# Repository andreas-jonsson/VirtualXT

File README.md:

# VirtualXT

VirtualXT is a Turbo PC/XT emulator for [libretro](https://www.libretro.com) that runs on modern hardware, operating systems and bare-metal ARM SBCs.
It is designed to be simple and lightweight yet still capable enough to run a large library of old application and games.

Browser version is avalible [here](https://realmode.games).

## Features

* Intel 286 processor
* PC/XT chipset
* Hardware CPU validator
* CGA or VGA compatible graphics
* EMS and UMA memory
* AdLib music synthesizer
* Serial UARTs
* Ethernet adapter
* Runs on bare-metal ARM
* Direct file share with host
* ISA passthrough​ using Arstech USB2ISA adapter
* GLaBIOS or Turbo XT BIOS 3.1 with extensions
* Integerated GDB server
* Flexible module system
* and more...

## Screenshots

## Build

The emulator is written in [Odin](https://odin-lang.org) and can be compiled using the included GNU Makefile.

```
git clone https://github.com/virtualxt/virtualxt.git
cd virtualxt
make release
# Or if you have RetroArch installed.
make run
```

You can download pre-built binaries from [itch.io](https://phix.itch.io/virtualxt/purchase).

## ISA Passthrough​

VirtualXT supports ISA passthrough using Arstech [USB2ISA](https://arstech.com/install/ecom-catshow/usb2.0.html) adapter or the [CH367](https://www.aliexpress.com/item/1005003569540792.html) development board.
It should be noted that DMA currently not supported and the CH367 board is **VERY** limited in it's capabilities.

## Hardware Validation

A hardware validator was developed to ensure proper CPU behaviour.
Some additional information about that can be found [here](https://hackaday.io/project/184209-virtualxt-hardware-validator).
This [talk](https://youtu.be/qatzd0niz9A?si=_NVqQu_zc1KDB8W6) by Daniel Balsom describes the process in details.

## Shout-out

Friends, contributors and sources of inspiration!

* **gloriouscow**
* **homebrew8088**
* **fmahnke**
* **adriancable**
* **mikechambers84**
* **trylle**
* **640-KB**

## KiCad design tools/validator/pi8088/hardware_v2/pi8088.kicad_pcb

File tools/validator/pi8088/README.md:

# PI8088 Hardware Validator

This is a hardware validator for testing instruction accuracy in 8088/V20 PC emulators. It plugs in the top/back of an RaspberryPi 4/400 computer and was built for testing the VirtualXT IBM PC/XT emulator. But it can easily be adopted for use with other emulators as well.

## Hardware
The hardware is very simple for this project. It is just a passive PCB that attaches to the RaspberryPi and connects any CMOS 8088 compatible CPU, like the 80C88 or NEC V20 to the RaspberryPi's GPIO pins. Something that should be noted is that the system is running on 3.3V and not 5V. Although that is out of spec for the CPU's in question it seems to run completely stable in the frequencies used here. 

## Software
On a software level the system works by first executing a setup programs that loads a CPU state that match the emulators state before the instruction in question was executed. It then lets the instruction execute on the attached CPU. Then proceeds by running a serialization program that retrieves the correct CPU state and compares it with the emulator's state after instruction execution. The user will then be presented with the diffs if any are found.

## Limitations
Although the cycle counts are reported, there are (at least in theory) situations where the exact count can not be trusted. The CPU is running in minimum mode which makes it hard to determine the exact status. For example, if a prefetch is performed during execution it is very complicated to determine how long the actual execution of the instruction took. It might be possible to resolve if the CPU is executing in maximum mode but that requires hardware changes. Software adjustments is needed if you want to test a V20 since not all status signals are decoded and the bus behavior is a little different.

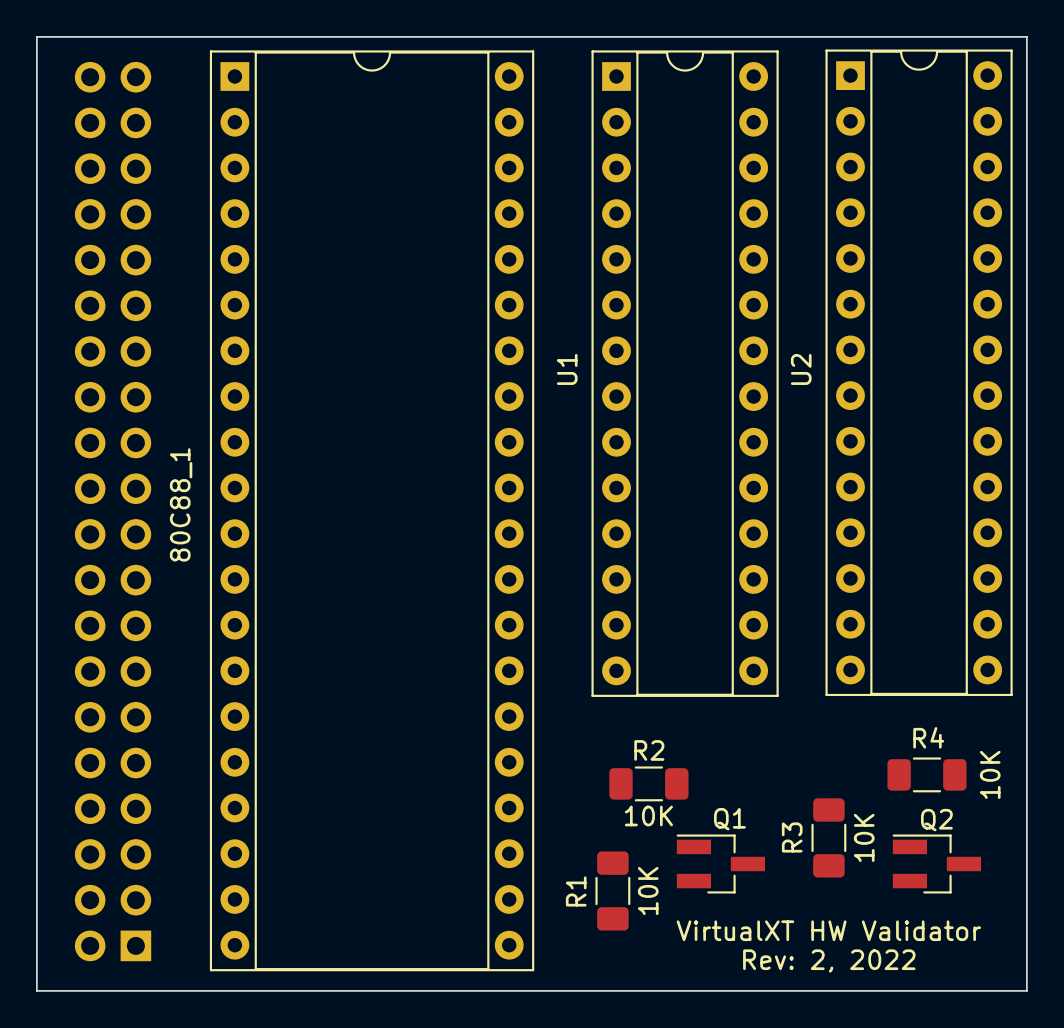
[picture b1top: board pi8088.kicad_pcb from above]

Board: 2 copper layers, 55.0 x 53.0 mm, 10 parts (1 on the bottom side), 35 nets, no tracks yet.

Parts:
80C88_1: 8088_Min_Mode; DIP-40_W15.24mm_Socket
GPIO_1: Raspberry_Pi_2_3; PinSocket_2x20_P2.54mm_Vertical
Q1, Q2: BSS138; SOT-23_Handsoldering
R1, R2, R3, R4: 10K; R_1206_3216Metric_Pad1.30x1.75mm_HandSolder
U1, U2: MCP23017_SP; DIP-28_W7.62mm_Socket

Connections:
/lv_shift/HV: 80C88_1.22 (READY), 80C88_1.33 (MN/~MX), 80C88_1.40 (VCC), GPIO_1.2 (5V), GPIO_1.4 (5V), R2.1, R4.1, U1.9 (VDD), U1.15 (A0), U2.9 (VDD)
/lv_shift/HVD1: Q1.3 (D), R2.2, U1.13 (SDA), U2.13 (SDA)
/lv_shift/HVD2: Q2.3 (D), R4.2, U1.12 (SCK), U2.12 (SCK)
/lv_shift/LV: GPIO_1.1 (3V3), GPIO_1.17 (3V3), Q1.1 (G), Q2.1 (G), R1.1, R3.1
/lv_shift/LVD1: GPIO_1.27 (ID_SD/GPIO0), Q1.2 (S), R1.2
/lv_shift/LVD2: GPIO_1.28 (ID_SC/GPIO1), Q2.2 (S), R3.2
unnamed: 80C88_1.1 (GND), 80C88_1.17 (NMI), 80C88_1.18 (INTR), 80C88_1.20 (GND), 80C88_1.31 (HOLD), GPIO_1.6 (GND), GPIO_1.9 (GND), GPIO_1.14 (GND), GPIO_1.20 (GND), GPIO_1.25 (GND), GPIO_1.30 (GND), GPIO_1.34 (GND), GPIO_1.39 (GND), U1.10 (VSS), U1.16 (A1), U1.17 (A2), U2.10 (VSS), U2.15 (A0), U2.16 (A1), U2.17 (A2)
unnamed: 80C88_1.2 (A14), U2.27 (GPA6)
unnamed: 80C88_1.3 (A13), U2.26 (GPA5)
unnamed: 80C88_1.4 (A12), U2.25 (GPA4)
unnamed: 80C88_1.5 (A11), U2.24 (GPA3)
unnamed: 80C88_1.6 (A10), U2.23 (GPA2)
unnamed: 80C88_1.7 (A9), U2.22 (GPA1)
unnamed: 80C88_1.8 (A8), U2.21 (GPA0)
unnamed: 80C88_1.9 (AD7), U2.8 (GPB7)
unnamed: 80C88_1.10 (AD6), U2.7 (GPB6)
unnamed: 80C88_1.11 (AD5), U2.6 (GPB5)
unnamed: 80C88_1.12 (AD4), U2.5 (GPB4)
unnamed: 80C88_1.13 (AD3), U2.4 (GPB3)
unnamed: 80C88_1.14 (AD2), U2.3 (GPB2)
unnamed: 80C88_1.15 (AD1), U2.2 (GPB1)
unnamed: 80C88_1.16 (AD0), U2.1 (GPB0)
unnamed: 80C88_1.19 (CLK), U1.5 (GPB4)
unnamed: 80C88_1.21 (RESET), U1.6 (GPB5)
unnamed: 80C88_1.23 (~TEST), U1.8 (GPB7)
unnamed: 80C88_1.25 (ALE), U1.7 (GPB6)
unnamed: 80C88_1.28 (IO/~M), U1.22 (GPA1)
unnamed: 80C88_1.29 (WR), U1.23 (GPA2)
unnamed: 80C88_1.32 (~RD), U1.24 (GPA3)
unnamed: 80C88_1.34 (~SSO), U1.21 (GPA0)
unnamed: 80C88_1.35 (A19/S6), U1.4 (GPB3)
unnamed: 80C88_1.36 (A18/S5), U1.3 (GPB2)
unnamed: 80C88_1.37 (A17/S4), U1.2 (GPB1)
unnamed: 80C88_1.38 (A16/S3), U1.1 (GPB0)
unnamed: 80C88_1.39 (A15), U2.28 (GPA7)

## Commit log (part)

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2023-09-06 First pass on Covox audio. WIP
2023-09-06 Deploying to gh-pages from @ andreas-jonsson/virtualxt@b364c19d4e3e002a4dcddade87100b181e20312b 🚀
2023-09-07 Reworked search paths.
2023-09-07 Changed buffer size.
2023-09-07 Resized buffer
2023-09-12 Added new CPU tests.
2023-09-12 Test cancelation
2023-09-12 Optimized premake script
2023-09-13 Switched to binary tests
2023-09-13 Use cppcheck --force
2023-09-14 Fixed bug in opcode FF.6
2023-09-15 Fixed a few more issues based on new tests.
2023-09-15 Added cycle check
2023-09-15 Exclude devices from test.
2023-09-15 Updated test excludes
2023-09-18 Added some minimal libc things.
2023-09-18 Deploying to gh-pages from @ andreas-jonsson/virtualxt@81c9cbf48ade9e95358b3b4b30e3ac53c2aac271 🚀
2023-09-18 Deploying to gh-pages from @ andreas-jonsson/virtualxt@b7076395af9b6c8488e11fbec7cf9625680b02ff 🚀
2023-09-18 Deploying to gh-pages from @ andreas-jonsson/virtualxt@1f78fcf46ec33975ce1083867473015214faf920 🚀
2023-09-18 SCANF_DISABLE_SUPPORT_FLOAT for now.
2023-09-22 Added frequency function to lua module
2023-09-22 Fixed name collision
2023-09-27 Should return 0 when started with --locate
2023-09-28 Updated version number
2023-10-07 Enable compilation for more unix platforms
2023-10-10 Updated version number.
2023-10-11 A better fix for relative lib loading
2023-10-11 rpath fix for OSX
2023-10-18 Bump @babel/traverse from 7.20.12 to 7.23.2 in /lib/simple-keyboard
    Bumps [@babel/traverse](https://github.com/babel/babel/tree/HEAD/packages/babel-traverse) from 7.20.12 to 7.23.2.
    - [Release notes](https://github.com/babel/babel/releases)
    - [Changelog](https://github.com/babel/babel/blob/main/CHANGELOG.md)
    - [Commits](https://github.com/babel/babel/commits/v7.23.2/packages/babel-traverse)
    ---
    updated-dependencies:
2023-10-19 Removed FDC module and updated ELKS image
2023-10-22 Improved EGA support
2023-10-23 VGA DAC fixes
2023-10-25 Deploying to gh-pages from @ andreas-jonsson/virtualxt@1660b8ebf0dce990bcef757dcaff9782873fdadf 🚀
2023-10-25 Removed CGA mode ctrl register from VGA module
2023-10-26 Fixed broken mode 13
2023-10-27 Default to VGA
2023-10-27 Fixed CGA init on web frontend
2023-10-28 Added turbo switch
2023-10-28 Default to V20
2023-10-29 Changed default frequency.
2023-11-01 update libretro makefile for newer emscripten sdk
2023-11-02 Fixed build issue on web frontend
2023-11-02 Fixed libretro compile issue
2023-11-02 Deploying to gh-pages from @ andreas-jonsson/virtualxt@5f3412cd23ef2f29018911460c91349cd1241ffc 🚀
2023-11-04 Added support for multiple fonts
2023-11-06 Added turbo text
2023-11-06 Fixed frequency switch code
2023-11-06 Added version number to help screen
2023-11-06 Updated SDL version
2023-11-08 Default to CGA
2023-11-08 Deploying to gh-pages from @ andreas-jonsson/virtualxt@6611c641465fa088d2752cda78ecf867b7e9aeb9 🚀
2023-11-10 Deploying to gh-pages from @ andreas-jonsson/virtualxt@78872a91a9a77c317ca415a3b89031ae37b24ed7 🚀
2023-11-10 Minor cleanup
2023-11-13 Removed 286 code
2023-12-04 Deploying to gh-pages from @ andreas-jonsson/virtualxt@1d31f4b3a1aacf71973f6d72af8b7be25c077387 🚀
2023-12-14 Added elks image to web build
2023-12-15 Experimental SLIP module
2023-12-18 Added emuctrl tool
2023-12-18 Deploying to gh-pages from @ andreas-jonsson/virtualxt@267b5676d5d64ba4b91a59717a6c80f9ec2e06dd 🚀
2023-12-20 Fixed premake script
2023-12-22 Added int28 detection
2023-12-22 Randomize VGA memory on startup
2024-01-10 Added USEUMBS tool
2024-01-10 More 286 support
2024-01-10 Print memory map on startup
2024-01-10 Better memory usage
2024-01-12 GDB can interrupt
2024-01-12 Added FRONTEND_CTRL_DEBUG command
2024-01-15 RIFS fixes
2024-01-16 Windows build fix
2024-01-16 Higher turbo frequency
2024-01-19 Fixed OSX build issue.
2024-01-19 RIFS default to home dir
2024-01-20 Added activity indicator for RIFS
2024-01-22 Added termbox2
2024-01-24 Load shell high!
2024-01-24 Deploying to gh-pages from @ andreas-jonsson/virtualxt@5db297a008655339af8db6b9a7852c817c4c243b 🚀
2024-01-25 Fixed RIFS free space issue
2024-01-31 Improved audio in web frontend.
2024-03-16 Bump follow-redirects from 1.15.1 to 1.15.6 in /lib/simple-keyboard
    Bumps [follow-redirects](https://github.com/follow-redirects/follow-redirects) from 1.15.1 to 1.15.6.
    - [Release notes](https://github.com/follow-redirects/follow-redirects/releases)
    - [Commits](https://github.com/follow-redirects/follow-redirects/compare/v1.15.1...v1.15.6)
    ---
    updated-dependencies:
    - dependency-name: follow-redirects
2024-03-23 Bump webpack-dev-middleware from 5.3.3 to 5.3.4 in /lib/simple-keyboard
    Bumps [webpack-dev-middleware](https://github.com/webpack/webpack-dev-middleware) from 5.3.3 to 5.3.4.
    - [Release notes](https://github.com/webpack/webpack-dev-middleware/releases)
    - [Changelog](https://github.com/webpack/webpack-dev-middleware/blob/v5.3.4/CHANGELOG.md)
    - [Commits](https://github.com/webpack/webpack-dev-middleware/compare/v5.3.3...v5.3.4)
    ---
    updated-dependencies:
2024-04-22 Test BSD build pipeline
2024-04-22 Switch to gmake
2024-04-22 Fixed build error on NetBSD
2024-04-23 Use pkgin
2024-04-23 Try add modular-xorg
2024-04-23 Removed PKG_PATH after install
2024-04-23 Unset PKG_PATH
2024-05-08 Removed NetBSD build for now
2024-06-12 Define _POSIX_C_SOURCE to expose popen & pclose
    popen and pclose aren't exposed by musl libc unless one of the following
    macros is defined:
    #if defined(_POSIX_SOURCE) || defined(_POSIX_C_SOURCE) \
    || defined(_X_OPEN_SOURCE) || defined(_GNU_SOURCE) \
    || defined(_BSD_SOURCE)
    According to popen(3) on Linux man-pages 6.05.01:
2024-06-18 Default to static modules and new built output path.
2024-06-18 Fixed build issues
2024-06-18 Updated libretro buildscript
2024-06-19 Fixed debug module for BSD systems
2024-06-20 Compile fixes for NetBSD
2024-06-27 Disabled networking for now.
2024-08-27 Minar cleanup and added gdb breakpoints from code
2024-08-27 Deploying to gh-pages from @ andreas-jonsson/virtualxt@ba0c232c30f3ebe63108909ebfc5408cbbafcc52 🚀
2024-08-27 Fixed misspelling
2024-08-28 Deploying to gh-pages from @ andreas-jonsson/virtualxt@ceb5baec2d1cdbdc91a3f40dbcf080be1c7ee065 🚀
2024-08-29 Fixed bug in network code
2024-08-29 Bump webpack from 5.40.0 to 5.94.0 in /lib/simple-keyboard
    Bumps [webpack](https://github.com/webpack/webpack) from 5.40.0 to 5.94.0.
    - [Release notes](https://github.com/webpack/webpack/releases)
    - [Commits](https://github.com/webpack/webpack/compare/v5.40.0...v5.94.0)
    ---
    updated-dependencies:
    - dependency-name: webpack
2024-09-03 BIOS update
2024-09-04 Fixed typo
2024-09-04 Deploying to gh-pages from @ andreas-jonsson/virtualxt@9559d299527ef9478d9604f044b906104184514d 🚀
2024-09-04 Fixed broken tests
2024-09-04 Fixed more broken tests
2024-09-05 Added AT chipset code
2024-09-11 Fixed compile issue
2024-09-11 Changed register structure.
2024-09-11 Run tests for AT branch
2024-09-13 New segment register layout.
2024-09-18 More pmode work
2024-09-18 Fixed instruction test 11 & FF.3
2024-09-18 Bump send and express in /lib/simple-keyboard
    Bumps [send](https://github.com/pillarjs/send) and [express](https://github.com/expressjs/express). These dependencies needed to be updated together.
    Updates `send` from 0.18.0 to 0.19.0
    - [Release notes](https://github.com/pillarjs/send/releases)
    - [Changelog](https://github.com/pillarjs/send/blob/master/HISTORY.md)
    - [Commits](https://github.com/pillarjs/send/compare/0.18.0...0.19.0)
    Updates `express` from 4.18.1 to 4.21.0
2024-09-19 Fixed PUSH SP test
2024-09-20 Added basic support for extended memory.
2024-09-23 Added more descriptor load functions.
2024-09-26 Faster GDB server
2024-09-30 Updated GDB module.
2024-09-30 More AT fixes.
2024-09-30 GDB server fixes
2024-09-30 Added missing header.
2024-10-01 Code cleanup
2024-10-01 Added schematics
2024-10-01 Deploying to gh-pages from @ andreas-jonsson/virtualxt@561e0a45eb43010b7299166d5520933e31fbc71d 🚀
2024-10-04 Code cleanup.
2024-10-05 Added FreeBSD build
2024-10-07 Set FreeBSD version
2024-10-10 More tests and bugfixes for V20/186
2024-10-11 Big code cleanup
2024-10-11 Added UMA support in BIOS extension.
2024-10-11 Deploying to gh-pages from @ andreas-jonsson/virtualxt@9ceb62d32340e541c57d45f53de2cf83f65fd036 🚀
2024-10-14 Minor code cleanup
2024-10-14 Deploying to gh-pages from @ andreas-jonsson/virtualxt@63e16eed721b72db23b0a35d3707108ee5da9ae5 🚀
2024-10-16 Updated BIOS and changed PPI turbo bit
2024-10-16 Updated emuctrl
2024-10-16 Updated API
2024-10-17 Fixed GDB trashing flags register on 286
2024-10-18 Fixed Windows build
2024-10-18 Changed to unsigned byte buffer
2024-10-18 FreeBSD fixes
2024-10-18 Code cleanup and build fixes
2024-10-18 Try cast value for Windows compatibility
2024-10-18 Fixed link issue on Windows
2024-10-18 More Windows fixes
2024-10-21 Added some config options
2024-10-22 Filter package in bridge to avoid UDP trafic.
2024-10-22 Deploying to gh-pages from @ andreas-jonsson/virtualxt@301fae5d8115d8072e2d3f1de212be1665abfe27 🚀
2024-10-24 Fixes for ARM build
2024-11-01 Added RPI frontend
2024-11-01 More RPI frontend fixes
2024-11-06 More RPI fixes
2024-11-11 RPI mouse fixed
2024-11-11 Added RPI build
2024-11-11 Fixed RPI build issues
2024-11-11 Added missing lib
2024-11-11 Added missing package step
2024-11-11 Added extra files
2024-11-11 Added missing boot files
2024-11-11 Deploying to gh-pages from @ andreas-jonsson/virtualxt@82ba915824c568f483c905f2275baf7e0f38c9c8 🚀
2024-11-12 Added RPI disk image
2024-11-12 Added RPI4 and ethernet support
2024-11-12 Fixed glob pattern
2024-11-12 Updated network code
2024-11-13 Try firce variable
2024-11-13 Fixed RPI4 build
2024-11-13 Switched web frontend to new disk interface.
2024-11-13 Deploying to gh-pages from @ andreas-jonsson/virtualxt@ac470824717feb8671176f01c561d51df7f0119b 🚀
2024-11-13 Fixed seek issue in disk interface.
2024-11-13 Deploying to gh-pages from @ andreas-jonsson/virtualxt@8668e3938064d955854f9930c8590eb31cac9b00 🚀
2024-11-14 Added kernel config options.
2024-11-15 Added VGA to RPI frontend
2024-11-19 Fixed audio on RPI frontend
2024-11-19 Fixed build script error
2024-11-19 Updated RPI README
2024-11-19 Started work on USB gamepads for RPI frontend
2024-11-21 Added basic RPI5 support
2024-11-21 More RPI5 fixes
2024-11-22 Fixed color issue on RPI5
2024-11-25 Better multicore support on RPI
2024-11-25 Play nice with slow SDCards
2024-11-26 Fixed HDMI audio
2024-11-26 Deploying to gh-pages from @ andreas-jonsson/virtualxt@14b5d3b15e76715ce945638693539a66da317500 🚀
2024-12-04 Added SCSI experiment
2024-12-04 Working CDROM
2024-12-06 Added support for Model-M keyboards. (SDL frontend only)
2024-12-06 Enabled libretro builds and updated Zig
2024-12-06 Updated libretro build
2024-12-06 Updated NDK URL
2024-12-06 Removed libretro riscv builds for now
2025-02-13 Added Odin codebase
2025-02-13 Added lld package to web build
2025-02-13 Fixed URL
2025-02-13 Testing libretro buildscript
2025-02-13 Export path in build
2025-02-13 Libretro buildscript updates
2025-02-14 Fixed initialization when using external linker
2025-02-14 Added MKPATH variable
2025-02-14 Try all 64bit libretro targets
2025-02-14 Added odin path
2025-02-14 Fixed syntax error in build script
2025-02-14 Added more debug info in buildscript
2025-02-14 Try to set OSX version
